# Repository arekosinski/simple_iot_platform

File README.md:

# simple_iot_system
System for gathering temperature and humidity based on SAM D21, Arduino and nrf24l01. Also Raspberry Pi is involved:)

# Parts of the system
1. Board with MCU, temperature & humidity sensor and radio (nrf24l01)
    * Board is based on Microchip SAM D21 microcontroller
    * You can use Arduino framework to play with this board (this board is Arduino Zero compatible - see more for reference in this [repo](https://github.com/arekosinski/samd21_minimal_board))
    * Radio module slot prepared for nrf24l01
    * Sensor for temp & humidity: SHT31
    * schematic is available in `sensor_schematic` directory. Board design is also attached
    * This board should take around 8-10uA in sleep mode
    * Other components
        * MCP16252 as voltage controller (as boost up). Designed for 2xAA batteries. Input voltage shouldn't excess 3.4V). Board voltage is 3V.
        * MOSFET On Semi FDC6306P (two on board) is used as power controller for radio module and other devices (3 gates)
        * One gate of FDC6306P is used as polarization protection between power source and MCP16252.
2. `sensor_node` - Code responsibile for communication with RF-RPI proxy
3. `rf_rpi_proxy` - Code for the board to act as a UART proxy to Raspberry Pi
4. `rpi_uart_client` - Python UART client resposible for translating received messages

# System diagram

# Why?
Just for fun :)

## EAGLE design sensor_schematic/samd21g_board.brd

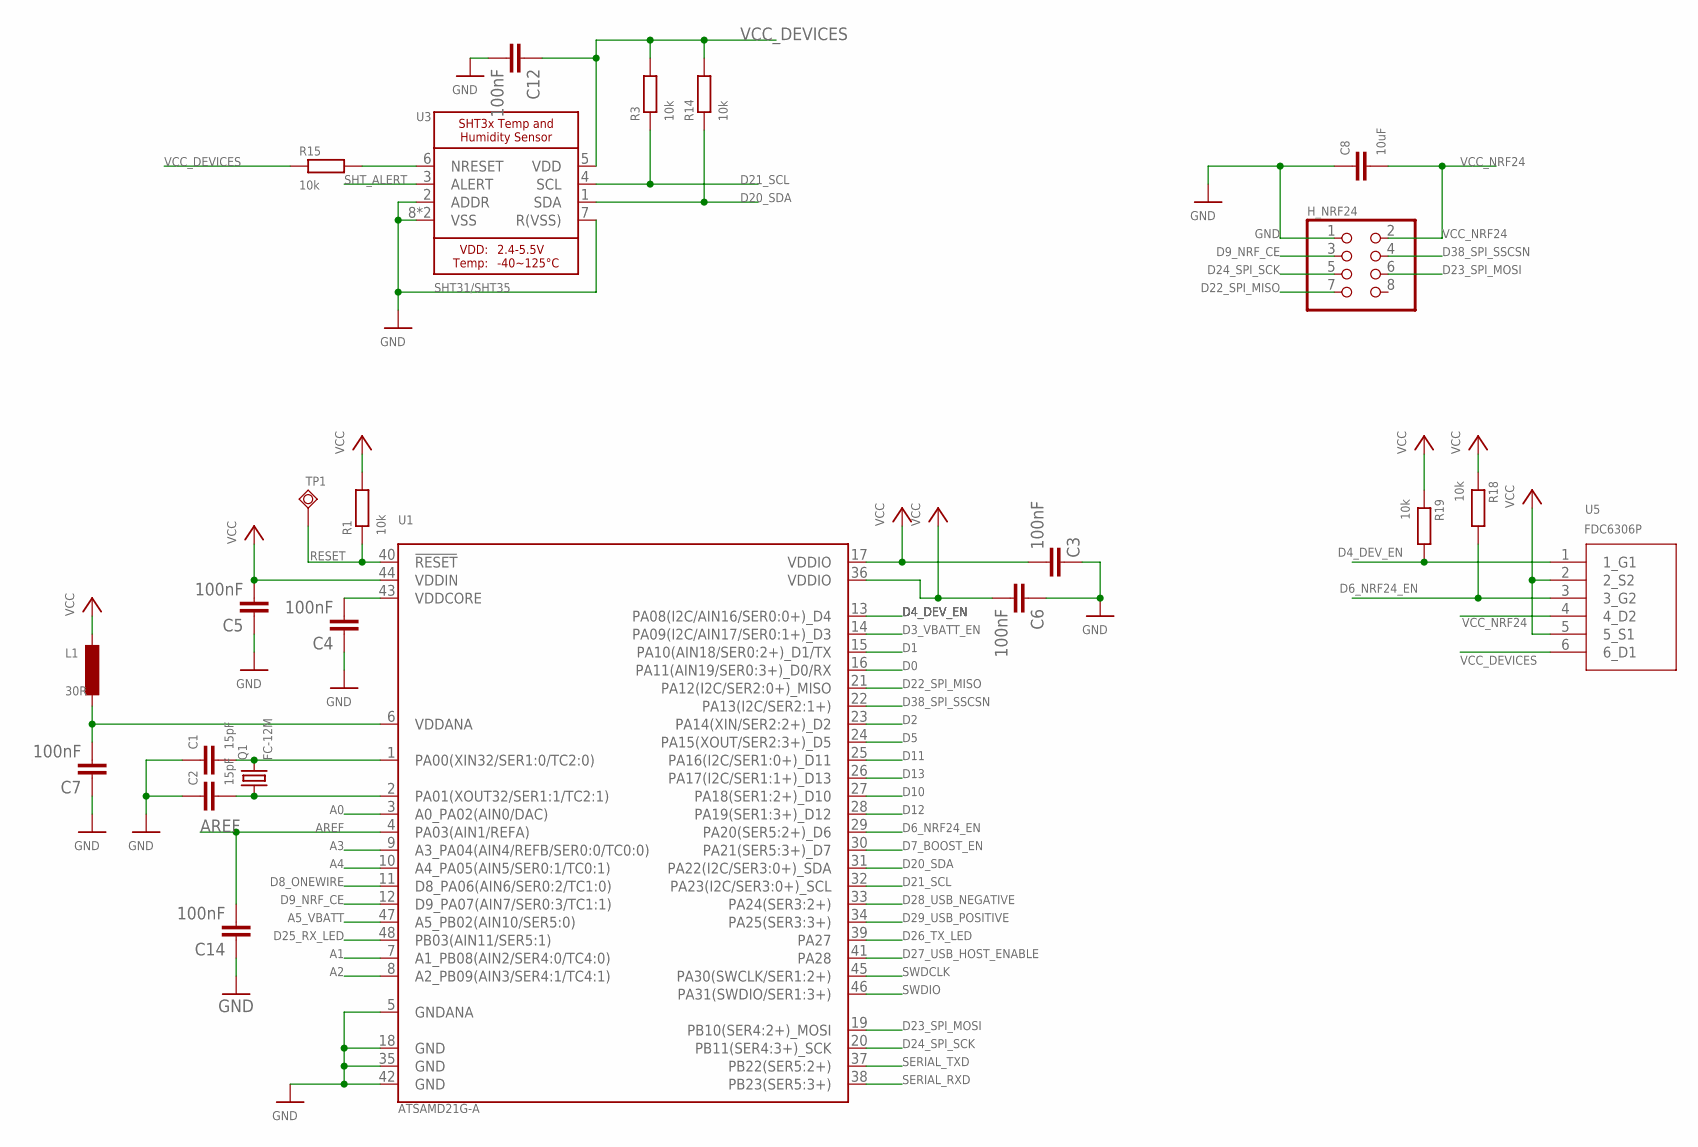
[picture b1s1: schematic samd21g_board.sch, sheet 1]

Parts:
C1, C2: 15pF; C0402
C3, C4, C5, C6, C7, C12, C14: 100nF; C0603
C8: 10uF; C0805
H_NRF24: PINHD-2X04_2.54; 2X04
L1: 30R; L3225M
Q1: FC-12M
R1, R3, R14, R15, R18, R19: 10k; R0805
TP1: TPSQTP13SQ; TP13SQ
U1: ATSAMD21G-A; TQFP-48
U3: SHT31/SHT35; SHT3X_DFN8
U5: FDC6306P; TSOT23-6_419BL_ONS

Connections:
A0: U1.3 (A0_PA02(AIN0/DAC)); also elsewhere on the board
A1: U1.7 (A1_PB08(AIN2/SER4:0/TC4:0)); also elsewhere on the board
A2: U1.8 (A2_PB09(AIN3/SER4:1/TC4:1)); also elsewhere on the board
A3: U1.9 (A3_PA04(AIN4/REFB/SER0:0/TC0:0)); also elsewhere on the board
A4: U1.10 (A4_PA05(AIN5/SER0:1/TC0:1)); also elsewhere on the board
A5_VBATT: U1.47 (A5_PB02(AIN10/SER5:0)); also elsewhere on the board
AREF: C14.2, U1.4 (PA03(AIN1/REFA)); also elsewhere on the board
D0: U1.16 (PA11(AIN19/SER0:3+)_D0/RX); also elsewhere on the board
D1: U1.15 (PA10(AIN18/SER0:2+)_D1/TX); also elsewhere on the board
D2: U1.23 (PA14(XIN/SER2:2+)_D2); also elsewhere on the board
D3_VBATT_EN: U1.14 (PA09(I2C/AIN17/SER0:1+)_D3); also elsewhere on the board
D4_DEV_EN: R19.2, U1.13 (PA08(I2C/AIN16/SER0:0+)_D4), U5.1 (1_G1)
D5: U1.24 (PA15(XOUT/SER2:3+)_D5); also elsewhere on the board
D6_NRF24_EN: R18.2, U1.29 (PA20(SER5:2+)_D6), U5.3 (3_G2)
D7_BOOST_EN: U1.30 (PA21(SER5:3+)_D7); also elsewhere on the board
D8_ONEWIRE: U1.11 (D8_PA06(AIN6/SER0:2/TC1:0)); also elsewhere on the board
D9_NRF_CE: H_NRF24.3, U1.12 (D9_PA07(AIN7/SER0:3/TC1:1))
D10: U1.27 (PA18(SER1:2+)_D10); also elsewhere on the board
D11: U1.25 (PA16(I2C/SER1:0+)_D11); also elsewhere on the board
D12: U1.28 (PA19(SER1:3+)_D12); also elsewhere on the board
D13: U1.26 (PA17(I2C/SER1:1+)_D13); also elsewhere on the board
D20_SDA: R14.1, U1.31 (PA22(I2C/SER3:0+)_SDA), U3.1 (SDA); also elsewhere on the board
D21_SCL: R3.1, U1.32 (PA23(I2C/SER3:0+)_SCL), U3.4 (SCL); also elsewhere on the board
D22_SPI_MISO: H_NRF24.7, U1.21 (PA12(I2C/SER2:0+)_MISO); also elsewhere on the board
D23_SPI_MOSI: H_NRF24.6, U1.19 (PB10(SER4:2+)_MOSI); also elsewhere on the board
D24_SPI_SCK: H_NRF24.5, U1.20 (PB11(SER4:3+)_SCK); also elsewhere on the board
D25_RX_LED: U1.48 (PB03(AIN11/SER5:1)); also elsewhere on the board
D26_TX_LED: U1.39 (PA27); also elsewhere on the board
D27_USB_HOST_ENABLE: U1.41 (PA28); also elsewhere on the board
D28_USB_NEGATIVE: U1.33 (PA24(SER3:2+)); also elsewhere on the board
D29_USB_POSITIVE: U1.34 (PA25(SER3:3+)); also elsewhere on the board
D38_SPI_SSCSN: H_NRF24.4, U1.22 (PA13(I2C/SER2:1+)); also elsewhere on the board
GND: C1.1, C2.1, C3.1, C4.1, C5.1, C6.1, C7.1, C8.1, C12.2, C14.1, H_NRF24.1, U1.5 (GNDANA), U1.18 (GND), U1.35 (GND), U1.42 (GND), U3.2 (ADDR), U3.7 (R(VSS)), U3.8 (VSS), U3.THERMAL (VSS); also elsewhere on the board
unnamed: C1.2, Q1.2, U1.1 (PA00(XIN32/SER1:0/TC2:0))
unnamed: C2.2, Q1.1, U1.2 (PA01(XOUT32/SER1:1/TC2:1))
unnamed: R15.2, U3.6 (NRESET)
unnamed: C7.2, L1.2, U1.6 (VDDANA)
unnamed: C4.2, U1.43 (VDDCORE)
RESET: R1.1, TP1.TP, U1.40 (!RESET!); also elsewhere on the board
SERIAL_RXD: U1.38 (PB23(SER5:3+)); also elsewhere on the board
SERIAL_TXD: U1.37 (PB22(SER5:2+)); also elsewhere on the board
SHT_ALERT: U3.3 (ALERT); also elsewhere on the board
SWDCLK: U1.45 (PA30(SWCLK/SER1:2+)); also elsewhere on the board
SWDIO: U1.46 (PA31(SWDIO/SER1:3+)); also elsewhere on the board
VCC: C3.2, C5.2, C6.2, L1.1, R1.2, R18.1, R19.1, U1.17 (VDDIO), U1.36 (VDDIO), U1.44 (VDDIN), U5.2 (2_S2), U5.5 (5_S1); also elsewhere on the board
VCC_DEVICES: C12.1, R3.2, R14.2, R15.1, U3.5 (VDD), U5.6 (6_D1); also elsewhere on the board
VCC_NRF24: C8.2, H_NRF24.2, U5.4 (4_D2)

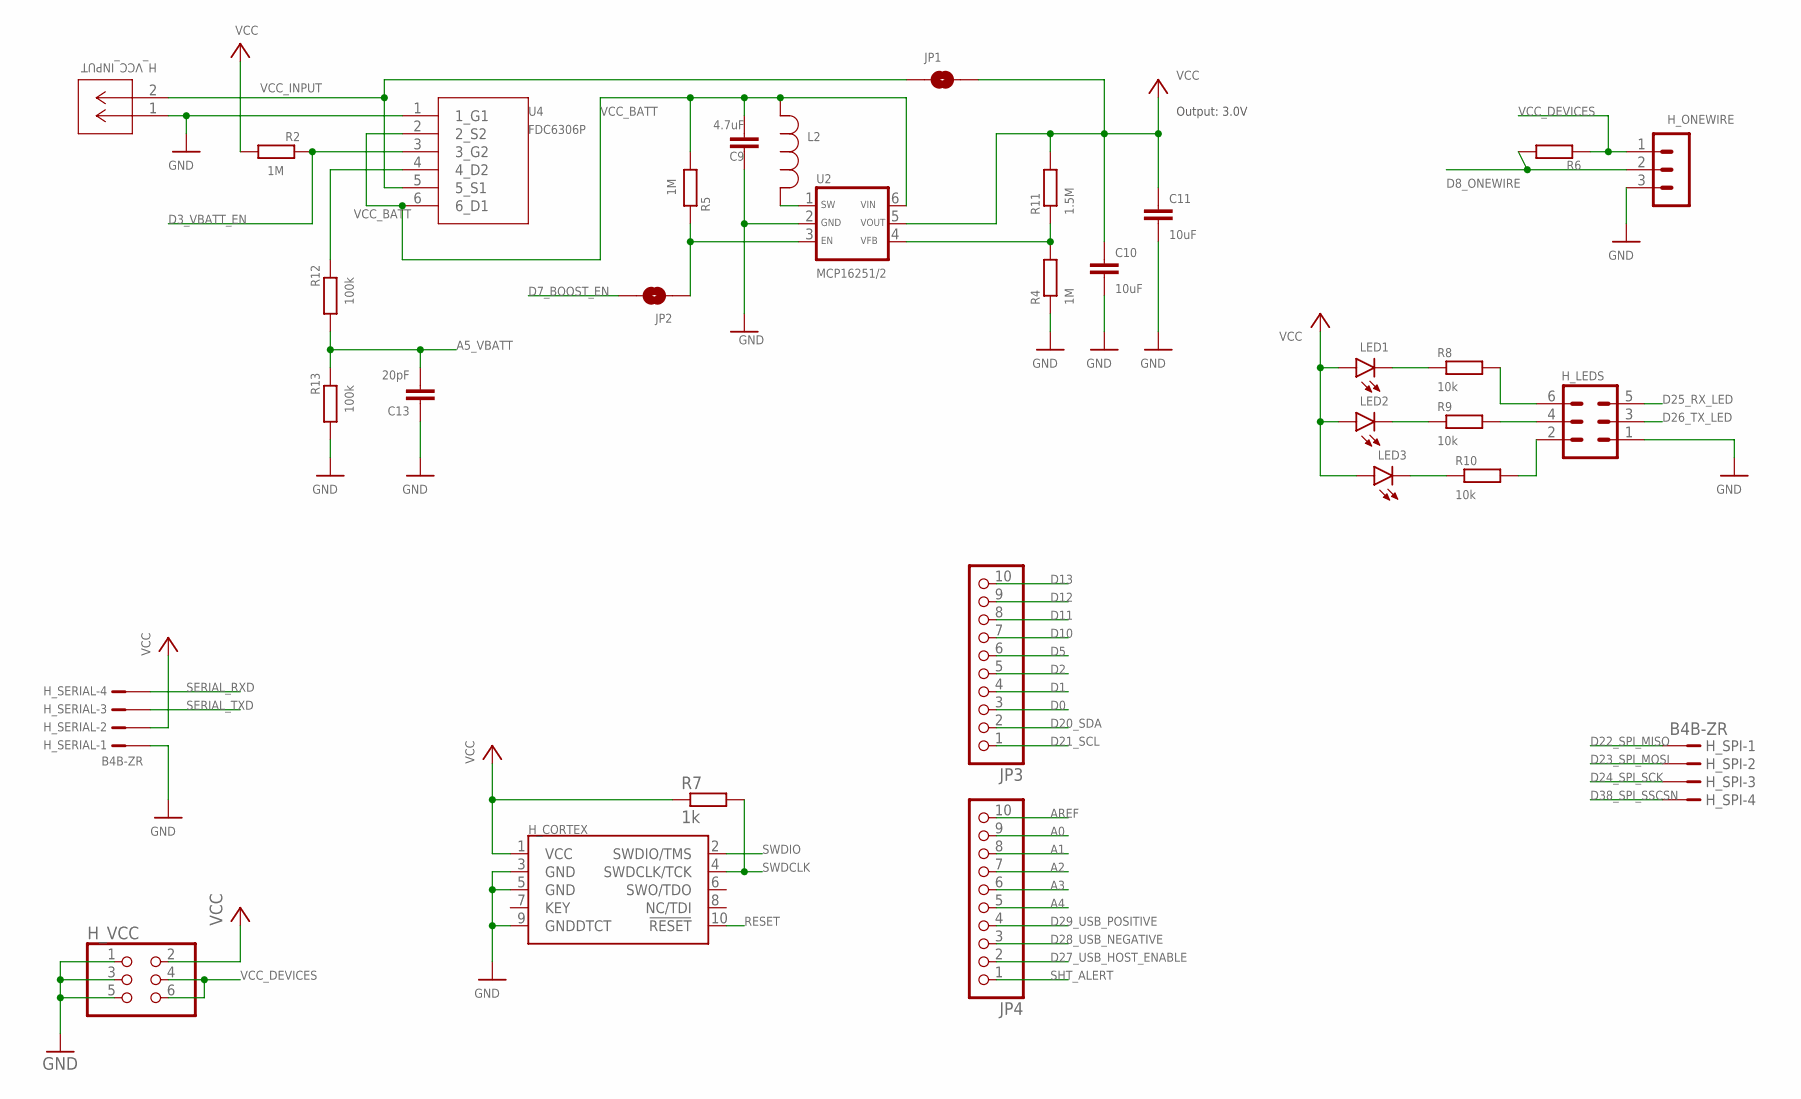
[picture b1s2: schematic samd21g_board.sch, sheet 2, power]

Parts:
C9: 4.7uF; C0805
C10, C11: 10uF; C0805
C13: 20pF; C0402
H_CORTEX: CORTEX_JTAG_DEBUG_PTH; 2X5-PTH-1.27MM
H_LEDS: M_2R03_50MIL-V2
H_ONEWIRE: M_1R03_50MIL-V
H_SERIAL: B4B-ZR
H_SPI: B4B-ZR
H_VCC: PINHD-2X03_2.54; 2X03
H_VCC_INPUT: S2B-ZR; CONN_S2B-ZR_JST
JP1, JP2: JUMPER-SMT_2_NO_NO-SILK; SMT-JUMPER_2_NO_NO-SILK
JP3, JP4: PINHD-1X10_2.54-S; 1X10-S
L2: 4.7uH; IND_CDRH3D16-4R7NC_SUM
LED1, LED2, LED3: LEDCHIP-LED0805; CHIP-LED0805
R2, R4, R5: 1M; R0805
R6: 4.7k; R0805
R7: 1k; R0805
R8, R9, R10: 10k; R0805
R11: 1.5M; R0805
R12, R13: 100k; R0805
U2: MCP16251/2; SOT-23-6
U4: FDC6306P; TSOT23-6_419BL_ONS

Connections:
A0: JP4.9; also elsewhere on the board
A1: JP4.8; also elsewhere on the board
A2: JP4.7; also elsewhere on the board
A3: JP4.6; also elsewhere on the board
A4: JP4.5; also elsewhere on the board
A5_VBATT: C13.2, R12.1, R13.2; also elsewhere on the board
AREF: JP4.10; also elsewhere on the board
D0: JP3.3; also elsewhere on the board
D1: JP3.4; also elsewhere on the board
D2: JP3.5; also elsewhere on the board
D3_VBATT_EN: R2.2, U4.3 (3_G2); also elsewhere on the board
D5: JP3.6; also elsewhere on the board
D7_BOOST_EN: JP2.2; also elsewhere on the board
D8_ONEWIRE: H_ONEWIRE.2, R6.2; also elsewhere on the board
D10: JP3.7; also elsewhere on the board
D11: JP3.8; also elsewhere on the board
D12: JP3.9; also elsewhere on the board
D13: JP3.10; also elsewhere on the board
D20_SDA: JP3.2; also elsewhere on the board
D21_SCL: JP3.1; also elsewhere on the board
D22_SPI_MISO: H_SPI.1; also elsewhere on the board
D23_SPI_MOSI: H_SPI.2; also elsewhere on the board
D24_SPI_SCK: H_SPI.3; also elsewhere on the board
D25_RX_LED: H_LEDS.5; also elsewhere on the board
D26_TX_LED: H_LEDS.3; also elsewhere on the board
D27_USB_HOST_ENABLE: JP4.2; also elsewhere on the board
D28_USB_NEGATIVE: JP4.3; also elsewhere on the board
D29_USB_POSITIVE: JP4.4; also elsewhere on the board
D38_SPI_SSCSN: H_SPI.4; also elsewhere on the board
GND: C9.1, C10.2, C11.2, C13.1, H_CORTEX.3 (GND), H_CORTEX.5 (GND), H_CORTEX.9 (GNDDTCT), H_LEDS.1, H_ONEWIRE.3, H_SERIAL.1, H_VCC.1, H_VCC.3, H_VCC.5, H_VCC_INPUT.1, R4.1, R13.1, U2.2 (GND), U4.1 (1_G1); also elsewhere on the board
unnamed: H_LEDS.4, R9.2
unnamed: LED2.C, R9.1
unnamed: LED3.C, R10.1
unnamed: LED1.C, R8.1
unnamed: H_LEDS.6, R8.2
unnamed: JP2.1, R5.2, U2.3 (EN)
unnamed: R12.2, U4.4 (4_D2)
unnamed: H_LEDS.2, R10.2
unnamed: R4.2, R11.1, U2.4 (VFB)
unnamed: L2.1, U2.1 (SW)
RESET: H_CORTEX.10 (!RESET); also elsewhere on the board
SERIAL_RXD: H_SERIAL.4; also elsewhere on the board
SERIAL_TXD: H_SERIAL.3; also elsewhere on the board
SHT_ALERT: JP4.1; also elsewhere on the board
SWDCLK: H_CORTEX.4 (SWDCLK/TCK), R7.2; also elsewhere on the board
SWDIO: H_CORTEX.2 (SWDIO/TMS); also elsewhere on the board
VCC: C10.1, C11.1, H_CORTEX.1 (VCC), H_SERIAL.2, H_VCC.2, JP1.2, LED1.A, LED2.A, LED3.A, R2.1, R7.1, R11.2, U2.5 (VOUT); also elsewhere on the board
VCC_BATT: C9.2, L2.2, R5.1, U2.6 (VIN), U4.2 (2_S2), U4.6 (6_D1)
VCC_DEVICES: H_ONEWIRE.1, H_VCC.4, H_VCC.6, R6.1; also elsewhere on the board
VCC_INPUT: H_VCC_INPUT.2, JP1.1, U4.5 (5_S1)

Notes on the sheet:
Output: 3.0V

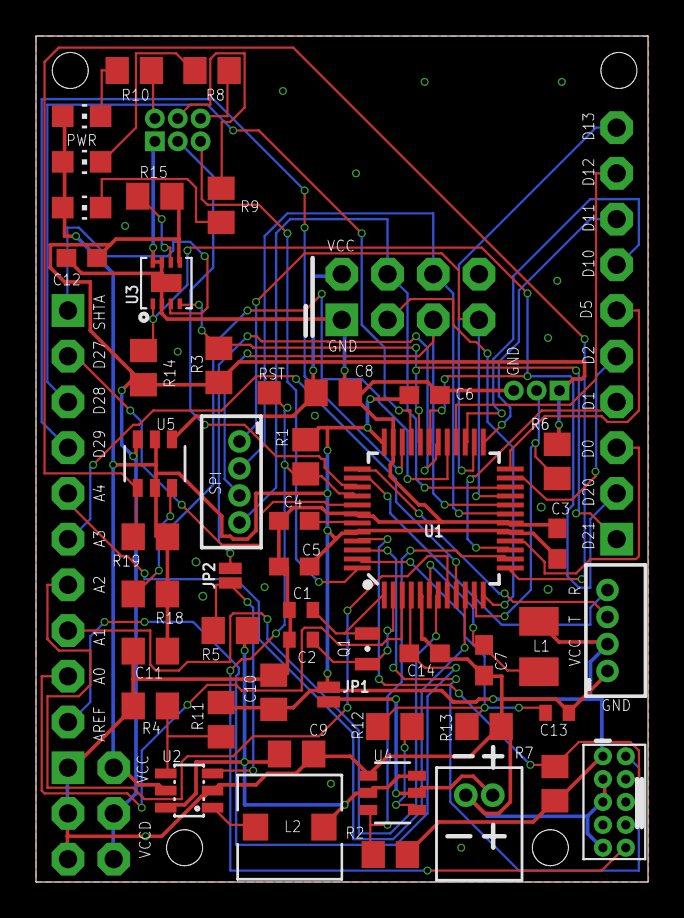
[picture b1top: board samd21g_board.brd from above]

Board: 2 copper layers, 34.0 x 47.0 mm, 55 parts (0 on the bottom side), 59 nets.

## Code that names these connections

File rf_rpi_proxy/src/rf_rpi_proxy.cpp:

#include <Arduino.h>

// define board pins according to arduino pins schema
#define LED_BUILTIN      (25ul)   // User controlled LED1 Arduino: D25 / Board: D25_RX_LED/PB03
#define LED_BUILTIN_1    LED_BUILTIN
#define LED_BULITIN_2    (26ul)   // User controlled LED2 Arduino: D26 / Board: D26_TX_LED/PA27
#define PIN_RADIO_EN     (6ul)	 // Pin to control radio power MOSFET / Arduino: D6 / Board: D6_NRF24_EN/PA20

// system behavior
#define SERIAL_BAUDS     (115200ul)	// UART Speed for debugging header (Arduino: Serial object)
#define RPI_SERIAL_BAUDS (230400ul) // UART Speed for communication with Raspberry Pi (Arduino: Serial1 object)

uint8_t is_debug_initialized = 0;

// headers for NRF24 library
#include <SPI.h>
#include "RF24.h"

// communication
#define R_PIN_CE         (9ul)		  // Arduino: D9 / Board: D9_NRF_CE/PA07
#define R_PIN_CSN        (38ul)		  // Arduino: D38 / Board: D38_SPI_SSCSN/PA13
#define R_ADDR_RX        (0x696900)	  // Address on which we must listen to get messages from remote nodes (on remote nodes this is TX address)
#define R_ADDR_WIDTH     (3ul)		  // We can limit frame by using shorter address
#define R_CHANNEL        (20ul)		  // Channel number from 2.4GHz range
#define R_POWER_LVL      RF24_PA_MAX  // Output power during sending
#define R_DATA_RATE      RF24_250KBPS // Data rate used over the air
#define R_MSG_DELAY      (50ul)		  // Check description of setRetries function for meaning of this value
#define R_MSG_RETRIES    (10ul)	      // Check description of setRetries function for meaning of this value

RF24 radio(R_PIN_CE, R_PIN_CSN);

/*
Enum with definition of possible system restart. User should be aware of what kind of reboot occurred.
1 - System reset
2 - External reset requested (some one pushedreset button)
3 - BOD 3.3V
4 - BOD 1.2V
5 - Normal power on reset - system is starting by its standard procedure
6 - WDT Reset
99 - Unknown / very very sad face :(
*/
typedef enum {
    /** (0) System reset */
    RBT_SYSTEM = 0,
    /** (1) External reset (reset pin) */
    RBT_EXTERNAL_RESET,
    /** (2) BOD 3.3V */
    RBT_BOD3V3,
    /** (3) BOD 1.2V */
    RBT_BOD1V2,
    /** (4) Normaln power on reset - standard */
    RBT_STARTUP,
    /** (6) WDT */
    RBT_WDT,
    RBT_UNKNOWN = 99
} startup_code_ref;

//
// debugging 
template <typename... T>
void debug_me(const char *str, T... args) {
#ifdef DEBUG_ENABLED
	if ( is_debug_initialized == 1 ) {
		int len = snprintf(NULL, 0, str, args...);
		if (len) {
			char buff[len] = {0};
			sprintf(buff, str, args...);
			Serial.print(buff);
		};
		Serial.println();
	};
#endif
}

void enable_debug_mode() {
#ifdef DEBUG_ENABLED
	PM->APBCMASK.reg |= PM_APBCMASK_SERCOM5;	
    Serial.begin(SERIAL_BAUDS);
	debug_me("----------------------------");
	debug_me("Debug enabled");
	is_debug_initialized = 1;
#endif
}

void disable_debug_mode() {
#ifdef DEBUG_ENABLED
	Serial.end();
	is_debug_initialized = 0;
#endif
}
// END debugging

startup_code_ref get_last_reset_cause() {
	if (PM->RCAUSE.bit.SYST == 1)
	{
		debug_me("Reboot: Reset requested by system");
		return RBT_SYSTEM;
	};
	if (PM->RCAUSE.reg & PM_RCAUSE_WDT)
	{
		debug_me("Reboot: WDT");
		return RBT_WDT;
	};
	if (PM->RCAUSE.bit.EXT == 1)
	{
		debug_me("Reboot: External reset requested");
		return RBT_EXTERNAL_RESET;
	};
	if (PM->RCAUSE.bit.BOD33 == 1)
	{
		debug_me("Reboot: Reset brown out 3.3V");
		return RBT_BOD3V3;
	};
	if (PM->RCAUSE.bit.BOD12 == 1)
	{
		debug_me("Reboot: Reset brown out 1.2v");
		return RBT_BOD1V2;
	};
	if (PM->RCAUSE.bit.POR == 1)
	{
		debug_me("Reboot: Normal power on reset");
		return RBT_STARTUP;
	};
	debug_me("Reboot: unknown reason");
	return RBT_UNKNOWN;
}

//
// basic function to shorthand (wrap) enabling and disabling devices
void enable_equipment(const uint8_t pinNumber, const PinStatus state = HIGH, const PinMode mode = OUTPUT) {
	debug_me("Enabling eq pin:%i state:%i mode:%i", pinNumber, state, mode);
	pinMode(pinNumber, mode);
	digitalWrite(pinNumber, state);
}

void disable_equipment(const uint8_t pinNumber, const PinStatus state = LOW, const PinMode mode = INPUT_PULLUP) {
	debug_me("Disabling eq pin:%i state:%i mode:%i", pinNumber, state, mode);
	digitalWrite(pinNumber, state);
	pinMode(pinNumber, mode);
}

// making LED blinking a bit easier
void say_hello_world(const int cycles_count = 2, const int delay_ms = 300, const int led_port = LED_BUILTIN) {
	for (int i = 0; i < cycles_count; i++)
	{
		enable_equipment(led_port, LOW);
		delay(delay_ms);
		disable_equipment(led_port, HIGH);
		if (i + 1 < cycles_count)
		{
			delay(delay_ms);
		};
	};
}


// configure radio
void init_radio() {
	enable_equipment(PIN_RADIO_EN, RADIO_EN_PIN_STATE, OUTPUT);
	delay(100);
	bool radio_being_status = radio.begin();
	if (!radio_being_status)
	{ // Radio failed to init. Give some time and perform reboot
		debug_me("Radio problem");
		say_hello_world(100, 200, LED_BUILTIN_1);
		NVIC_SystemReset();
	};

	radio.enableDynamicPayloads();

	radio.setAutoAck(true);
	radio.setChannel(R_CHANNEL);
	radio.setAddressWidth(R_ADDR_WIDTH);
	radio.setPALevel(R_POWER_LVL);
	radio.setDataRate(R_DATA_RATE);
	radio.setRetries(R_MSG_DELAY, R_MSG_RETRIES);

	radio.openReadingPipe(1, R_ADDR_RX);

#ifdef DEBUG_ENABLED
	radio.printDetails();
	radio.printPrettyDetails();
#endif

	radio.startListening();
}
// radio functions


void loop() {
	debug_me("Start listening for new messages");
	radio.startListening();
	char msg[33] = {'\0'}; // max possible message size is 32bytes for nrf24l01

	while (!radio.available())
	{
		// waiting for new message
		// TODO: in next version we should use interrupt from NRF to handle newly arrived messages
	};

	// process new message
	if (radio.available())
	{
		uint8_t msg_len = radio.getDynamicPayloadSize();
		radio.read(&msg, msg_len);
		Serial1.println(msg);
#ifdef DEBUG_ENABLED
		debug_me(msg);
		say_hello_world(1, 10, LED_BULITIN_2);
#endif
	};
}

void setup(void) {

	enable_debug_mode();
	debug_me("System start");
	say_hello_world(3, 200);

	startup_code_ref startup_code = get_last_reset_cause();

	Serial1.begin(RPI_SERIAL_BAUDS);
	// say hi to Raspberry Pi
	Serial1.println("X: Welcome");
	Serial1.print("X: Last reboot code: ");
	Serial1.println(startup_code);
	init_radio();
}

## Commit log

2021-05-05 initial version of small board based on SAM D21 with schematic and code for transmitter and receiver
2021-05-13 cleaning up repo
2021-05-13 reducing messages length
2021-05-17 communication between board and RPi over UART
2021-05-22 small fixes
2021-05-22 very short readme
2021-05-22 readme
2021-05-23 get stats about retransmissions from nrf module
2021-06-11 addig watchdog features and small fixes
2021-08-26 ability to set up alternative node ID
2021-10-14 adding additional power source - accu charged from solar panels
2022-10-01 libraries update & configuration changes
2022-10-01 adjust serial speed to board
2025-02-07 small changes

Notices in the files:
parts and their libraries:
SparkFun-Connectors: Licensing: Creative Commons ShareAlike 4.0 International - https://creativecommons.org/licenses/by-sa/4.0
common_used_objects: COPYRIGHT: Copyright (C) 2018 Accelerated Designs. All rights reserved
